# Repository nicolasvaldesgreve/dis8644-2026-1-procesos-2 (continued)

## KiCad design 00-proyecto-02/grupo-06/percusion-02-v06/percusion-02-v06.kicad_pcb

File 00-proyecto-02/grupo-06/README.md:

# proyecto-02

## Grupo

Número de grupo: 06

Tema del grupo: **Percutores**. 

Integrantes:

- Catalina Catalán / [06-terroiblea](https://github.com/terroiblea/dis8644-2026-1-procesos-2/tree/main/06-terroiblea)
- Martina Echavarría / [10-martinaechavarria-stack](https://github.com/terroiblea/dis8644-2026-1-procesos-2/tree/main/10-martinaechavarria-stack)
- Nicolás Miranda / [18-Nicolas-Miranda1312](https://github.com/terroiblea/dis8644-2026-1-procesos-2/tree/main/18-Nicolas-Miranda1312)
- Vania paredes / [24-paredesvania](https://github.com/terroiblea/dis8644-2026-1-procesos-2/tree/main/24-paredesvania)
- Carla Pino / [25-coff4](https://github.com/terroiblea/dis8644-2026-1-procesos-2/tree/main/25-Coff4)

## Circuito 1

Lub-dub.  

### Descripción general/conceptual 1

Lub-dub hace exactamente lo que hace un corazón: **bombea**. Pero en vez de bombear sangre, bombea pulsos eléctricos. En vez de mantener vivo a un organismo, **mantiene vivo el ritmo**. Lub-dub late. A veces  *Tac. Tac. Tac*. Otras, *Dumb. Dumb. Dumb*. Con la misma indiferencia biológica con que tu corazón te despertó esta mañana, Lub-dub bombea energía guiada por un compás. Es un percutor. Es un metrónomo pero con actitud.

#### ¿Qué hace Lub-dub por ti?

- Permite ajustar el tempo y el carácter del golpe, desde un latido tranquilo de persona en reposo hasta los 180bpm de alguien que acaba de ver su nota de taller.
- Es clínicamente superior a un metrónomo porque suena cool y los metrónomos no.
- Científicos del Instituto Cardiovascular de Sonidos Raros han determinado que escuchar Lub-dub mientras estudias mejora la concentración en un 340%. Este dato no ha sido verificado.

### Descripción de funcionamiento 1

Lub-dub recibe 12V por un jack de alimentación, regulados internamente a 5V con un L7805. Su output es una señal de audio por un jack estéreo. Tiene cuatro potenciómetros que en conjunto controlan el tempo y el carácter del golpe.

El corazón del circuito es un oscilador construido con inversores Schmitt-trigger de los chips 40106 y 4069UBE. Un condensador se carga y descarga continuamente a través de resistencias variables: los potenciómetros cambian esas resistencias, lo que cambia qué tan rápido se carga el condensador y por lo tanto qué tan rápido late y cómo suena ese latido. La ventaja del Schmitt-trigger es que conmuta en voltajes distintos al subir y al bajar, lo que produce ese golpe brusco y limpio en vez de una transición suave. Antes de llegar al output, la señal pasa por una red de condensadores y resistencias que recorta el pulso y lo convierte en un impulso corto y acentuado. Ese recorte es lo que transforma la oscilación en un *tac* o un *dumb* dependiendo de cómo estén ajustados los potenciómetros.

### Falstad 1

Antes de armar cada circuito realizamos un testeo del flujo de la corriente de cada circuito. 

### Esquemático 1

Esquemático referencia 1: Logic Noise: Filters And Drums de Hackaday.

Esquemático intervenido:

### PCB 1

La imagen de referencia para desarrollar el diseño de la PCB fue sacada de internet (link en referencias bibliográficas)

### Documentación audiovisual 1

#### Video funcionamiento protoboard 1

#### Video proceso y cambios protoboard 1

## Circuito 2

Barry Benson.  

### Descripción general/conceptual 2

Barry Benson no es una abeja. **Es peor que una abeja**, es una abeja con complejos, quiere ser una mosca. Tiene la capacidad sobreinsectoide de reproducir exactamente ese sonido de mosca agonizante atrapada entre tu oreja y la almohada a las 3 de la madrugada. Es la representación en silicio de ese sonido, **Barry Benson pega zumbidos**. Un zumbido ondulante que sube y baja de intensidad como si el insecto se acercara y alejara de tu oído a voluntad propia. La ciencia no puede explicar del todo por qué suena exactamente así. Nosotros tampoco. Pero lo hace.

#### ¿Qué hace Barry Benson por ti?

- Reproduce con fidelidad perturbadora el sonido de un insecto atrapado entre tu oreja y la almohada.
- Permite ajustar el zumbido con cuatro potenciómetros para encontrar el tono exacto que más molesta a tu compañero de pieza.
- Según investigaciones del prestigioso Instituto de Zumbidología Aplicada de Concepción, la exposición prenatal al sonido de Barry Benson produce niños con oído absoluto y una relación complicada con los insectos.
- Suena como *bzzzZZZzzzbzzZZZZzbzz*. Como si alguien hubiera atrapado una abeja en un sintetizador analógico y ninguno de los dos estuviera contento con la situación.
  
### Descripción de funcionamiento 2

Barry Benson recibe 12V por un jack de alimentación, que el circuito reduce internamente a 5V usando un regulador L7805. Su único output es una señal de audio por un jack estéreo.

Cuando alguien usa Barry Benson, interactúa con cuatro potenciómetros. Cada uno controla la frecuencia de un oscilador independiente, en otras palabras, es básicamente qué tan rápido vibra cada "ala" de la abeja. El chip que hace posible todo esto es el 40106, que contiene seis inversores Schmitt-trigger, componentes que deciden cuándo una señal es alta o baja, produciendo oscilaciones estables. Las cuatro señales resultantes se mezclan a través de compuertas XOR del chip 4070. Una XOR produce señal solo cuando sus entradas son distintas, así que al combinar frecuencias similares pero no idénticas, la salida fluctúa a una velocidad igual a la diferencia entre ambas. Ese fenómeno es lo que hace que el volumen suba y baje de forma orgánica y le da a Barry ese carácter de insecto vivo que ningún preset de sintetizador ha logrado replicar con tanta dignidad.

### Falstad 2

### Esquemático 2

Esquemático referencia: Inharmonic square waves (página 238) de Make: Electronic Music from scratch.

Esquemático intervenido: 

### PCB 2

La imagen de referencia para desarrollar el diseño de la PCB fue sacada de internet (link en referencias bibliográficas)

### Documentación audiovisual 2

#### Video funcionamiento protoboard 2

#### Video proceso y cambios protoboard 2

## BOM

| Componente | Tipo | Cantidad | Precio (c/u) | Comprar |
|------------|------|----------|--------------|---------|
| Chip 4069UBE | Circuito Integrado | 1 | $1.100 | [Cabeza Cuadrada](https://www.cabezacuadrada.cl/product/cd4069/) |
| Chip CD40106BE | Circuito Integrado | 2 | $750 | [Cabeza Cuadrada](https://www.cabezacuadrada.cl/product/cd40106be/) |
| Potenciómetro 100K | Potenciómetro | 4 |  $490 | [Mechatronic Store](https://www.mechatronicstore.cl/potenciometro-rotacional-10k/) |
| Potenciómetro 250K | Potenciómetro | 4 | $495 | [Altronics](https://altronics.cl/potenciometro-lineal-250k-b250k) |
| Capacitor no polarizado 100nF | Condensador Cerámico | 6 |  $100 | [Mechatronic Store](https://www.mechatronicstore.cl/condensadores-ceramicos-distintos-valores/) |
| Capacitor no polarizado 10nF | Condensador Cerámico | 1 | $100 | [Mechatronic Store](https://www.mechatronicstore.cl/condensadores-ceramicos-distintos-valores/) |
| Capacitor polarizado 10uF 50V | Condensador Electrolítico | 6 |  $100 | [Mechatronic Store](https://www.mechatronicstore.cl/condensador-capacitorio-de-electrolitico-por-unidad-varios-valores/) |
| Capacitor polarizado 0.22uF 50V | Condensador Electrolítico | 1 |  $100 | [Mechatronic Store](https://www.mechatronicstore.cl/condensador-capacitorio-de-electrolitico-por-unidad-varios-valores/) |
| Capacitor polarizado 100uF 50V | Condensador Electrolítico | 4 | $100 | [Mechatronic Store](https://www.mechatronicstore.cl/condensador-capacitorio-de-electrolitico-por-unidad-varios-valores/) |
| Capacitor polarizado 1uF 50V | Condensador Electrolítico | 1 | $100 | [Mechatronic Store](https://www.mechatronicstore.cl/condensador-capacitorio-de-electrolitico-por-unidad-varios-valores/) |
| Resistencia 100K | Resistencia 1/2W | 1 |  $100 | [Mechatronic Store](https://www.mechatronicstore.cl/resistencias-electricas-1-2-w-1-unidad/) |
| Resistencia 1K | Resistencia 3W | 4 |  $200 | [Mechatronic Store](https://www.mechatronicstore.cl/resistencias-electricas-3w-por-unidad/) |
| Diodo 1N4007 | Diodo Rectificador | 2 | $200 | [Mechatronic Store](https://www.mechatronicstore.cl/diodo-rectificador-in4007-1n4007-4007/) |
| LED 3mm/5mm | LED | 3 |  $100 | [Mechatronic Store](https://www.mechatronicstore.cl/led-3mm-5mm/) |
| Regulador de voltaje L7805 | Regulador 5V DC | 2 | $490 | [Mechatronic Store](https://www.mechatronicstore.cl/regulador-limitador-de-voltaje-5v-dc/) |
| Chip CD4070BE | Circuito Integrado | 1 | - | [Mouser](https://www.mouser.cl/ProductDetail/Texas-Instruments/CD4070BE?qs=5WY7Uqh921w5Ya0dPgjorQ%3D%3D) |
| Protoboard 830 puntos | Protoboard MB102 | 2 | $3.790 | [Mechatronic Store](https://www.mechatronicstore.cl/breadboard-830-puntos-mb102/) |
| Barrel Jack Switch | Conector | 4 | — | Extraídos del LID |
| Switch 2 pines, 2 posiciones | Interruptor On/Off | 2 | $570 | [Katode](https://www.katode.cl/switches/1339-interruptor-switch-2-pines-on-off-corto.html) |

## Otros circuitos 

### Amplificador/salida 

Usamos la base anteriormente vista en el proyecto 01 con el Chip 386; circuito temporal de amplificador para sonar más alto y poder modificar el sonido final. Al modificarse ciertos parámetros (condensadores) cada placa sonaba distinto. Barry Benson funciona mejor con condensadores menores a 100 μF y Lub-dub funciona mejor con condensadores de 100 μF.    

## Colaboración con otros grupos

### ¿Cómo ayudamos a otros grupos?

#### Carla Pino:

- Ayudó a dos grupos a subir de forma correcta las carpetas del proyecto 2, específicamente el apartado de las versiones de esquemáticos y PCB. 
- Ayudó a distintos grupos a instalar bibliotecas externas de KiCad.

#### Martina Echavarría: 

- Ayudó a *Grupo 01* a cargar su batería.

#### Vania Paredes, Catalina Catalán y Nicolás Miranda: 

- Ayudaron a *Grupo 04* en indicar e instruir cómo conectar barrel y audio jack.

#### Nicolás Miranda: 

- Ayudó a *Grupo 05* a poner y buscar huellas en KiCad. 

### ¿Cómo nos ayudó otro grupo?

- El *Grupo 01* nos ayudó con las huellas (recordar comandos). 
- El *Grupo 01* nos prestó su batería para grabar porque la de nosotros se quedó sin carga.

Agradecimiento especial a Sebastián Sáez (Sae porque sabe) que si bien no es del curso siempre está en el lid para prestarnos su super ayuda.

## Bibliografía

### Referencias Bibliográficas

- Akther, S. (s.f). *Vectores corazón real*. Vecteezy. <https://es.vecteezy.com/arte-vectorial/67973094-anatomico-humano-corazon-ilustraciones-anatomia-medico>
- Pearson, K. (2024). *Make: Electronic Music from scratch*. Make Community, LLC.  
- Stock,M. (25 de Febrero, 2026). *Silueta simple en negro y blanco de una abeja*.  Shutterstock. <https://www.shutterstock.com/es/image-vector/simple-black-white-silhouette-bee-representing-2743356303>
- Williams, E. (25 de Marzo, 2015). *Logic Noise: Filters And Drums*. Hackaday. <https://hackaday.com/2015/03/25/logic-noise-filters-and-drums/>

### Bibliografía investigación

- Klein, M. [@MoritzKlein0](10 de Agosto, 2023). *Designing a simple analog kick drum from scratch* [video]. Youtube. https://youtu.be/yz37Yz315eU
- Klein, M. [@MoritzKlein0](19 de Abril, 2024). *Designing a TR-808 style snare drum from scratch* [video]. Youtube. <https://youtu.be/hULEn2_4Unw>
- Klein, M. [@MoritzKlein0](5 de Diciembre, 2023). *Diseñando un hi-hat estilo TR-606 desde cero* [video]. Youtube. <https://youtu.be/zbBY7JL9nnQ>
- Pekkarinen, L. [@krakenpine](6 de Diciembre, 2020). *Diy Twin-T kick drum eurorack module demo* [video]. Youtube. <https://youtu.be/iETSEz60OVA>
- Pekkarinen, L. (2024). *k
rakenpine-synthing*. GitHub. 
<https://github.com/Krakenpine/krakenpine-synthing/tree/main>
- Newton C. (s.f). *Generadores de Percusión (ART858S)*. INCB. <https://www.incb.com.mx/index.php/articulos/9-articulos-tecnicos-y-proyectos/9910-generadores-de-percusion-art858s>
- Newton C. (s.f). *Generador de Percusión Para Ritmos Musicales (ART1596S)*. INCB. <https://newtoncbraga.com.mx/articulos/9-articulos-tecnicos-y-proyectos/31055-generador-de-percusion-para-ritmos-musicales-art1596s>
- Richardson, R. (23 de Marzo, 2013) *Twin T drum osc with 555 trigger*. Cirfcuit-Lab. <https://www.circuitlab.com/circuit/eykayh/twin-t-drum-osc-with-555-trigger/>

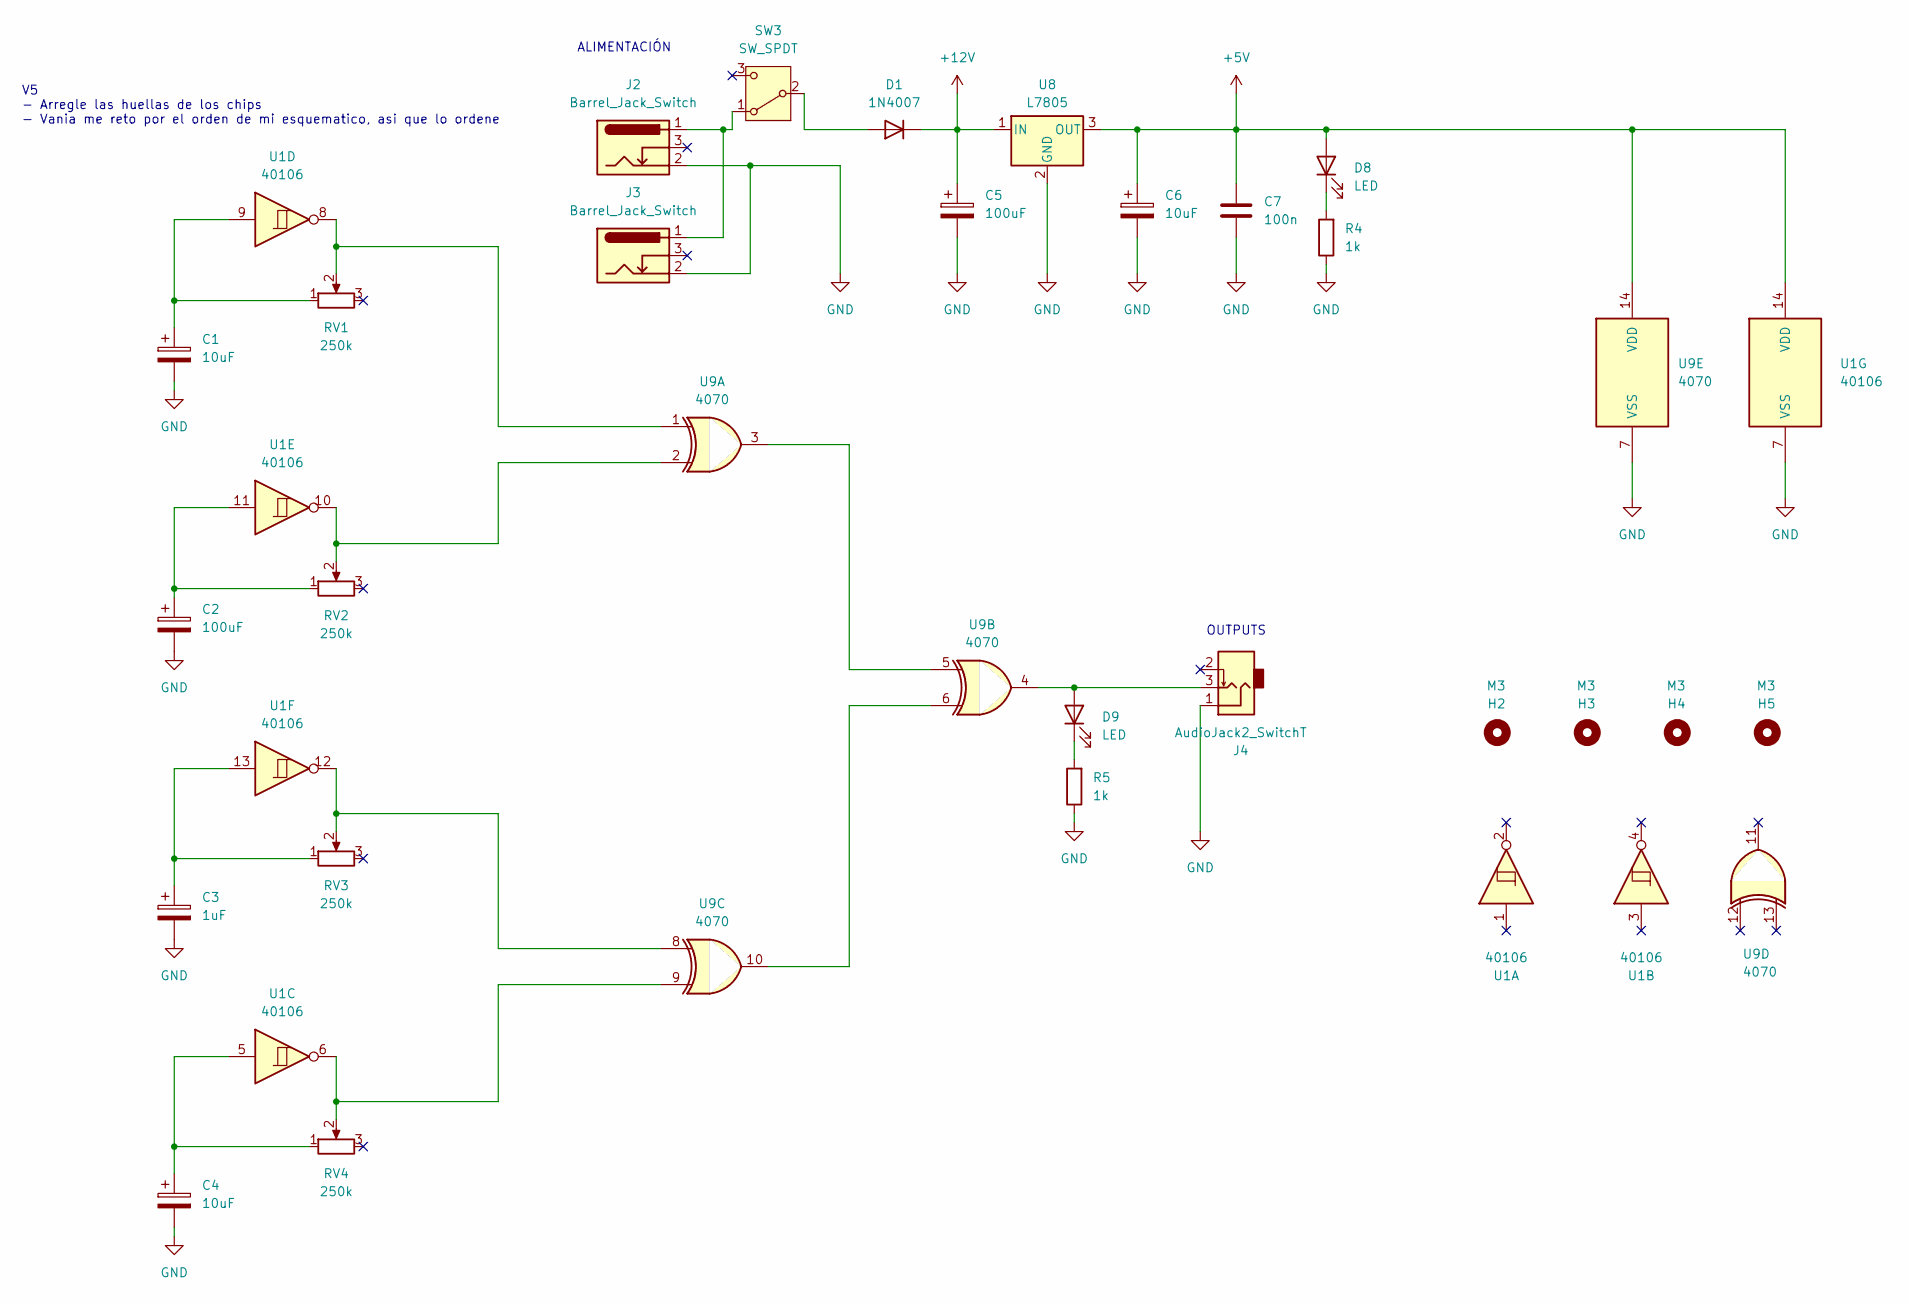
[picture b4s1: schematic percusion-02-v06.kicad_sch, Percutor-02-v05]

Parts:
C1, C4: 10uF; CP_Radial_D8.0mm_P3.80mm
C2, C5: 100uF; CP_Radial_D8.0mm_P3.80mm
C3: 1uF; CP_Radial_D8.0mm_P3.80mm
C6: 10uF; CP_Radial_D4.0mm_P2.00mm
C7: 100n; C_Disc_D5.0mm_W2.5mm_P2.50mm
D1: 1N4007; D_DO-41_SOD81_P10.16mm_Horizontal
D8, D9: LED; LED_D5.0mm
H2, H3, H4, H5: M3; MountingHole_3.2mm_M3
J2, J3: Barrel_Jack_Switch; BarrelJack_Horizontal
J4: AudioJack2_SwitchT; PJ301M-12
R4, R5: 1k; R_Axial_DIN0207_L6.3mm_D2.5mm_P10.16mm_Horizontal
RV1, RV2, RV3, RV4: 250k; Potentiometer_Alps_RK163_Single_Horizontal
SW3: SW_SPDT; spdt_ssd12d00g3
U1: 40106; DIP-14_W7.62mm_LongPads
U8: L7805; TO-220-3_Horizontal_TabDown
U9: 4070; DIP-14_W7.62mm_LongPads

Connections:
+5V: C6.1, C7.1, D8.2 (A), U1.14 (VDD), U8.3 (OUT), U9.14 (VDD)
+12V: C5.1, D1.1 (K), U8.1 (IN)
GND: C1.2, C2.2, C3.2, C4.2, C5.2, C6.2, C7.2, J2.2, J3.2, J4.1, R4.1, R5.1, U1.7 (VSS), U8.2 (GND), U9.7 (VSS)
unnamed: C1.1, RV1.1, U1.9
unnamed: C2.1, RV2.1, U1.11
unnamed: C3.1, RV3.1, U1.13
unnamed: C4.1, RV4.1, U1.5
unnamed: D1.2 (A), SW3.2 (B)
unnamed: D8.1 (K), R4.2
unnamed: D9.2 (A), J4.3, U9.4
unnamed: D9.1 (K), R5.2
unnamed: RV1.2, U1.8, U9.1
unnamed: RV2.2, U1.10, U9.2
unnamed: RV3.2, U1.12, U9.8
unnamed: RV4.2, U1.6, U9.9
unnamed: J2.1, J3.1, SW3.1 (A)
unnamed: U9.3, U9.5
unnamed: U9.6, U9.10

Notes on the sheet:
ALIMENTACIÓN
OUTPUTS
V5 - Arregle las huellas de los chips - Vania me reto por el orden de mi esquematico, asi que lo ordene

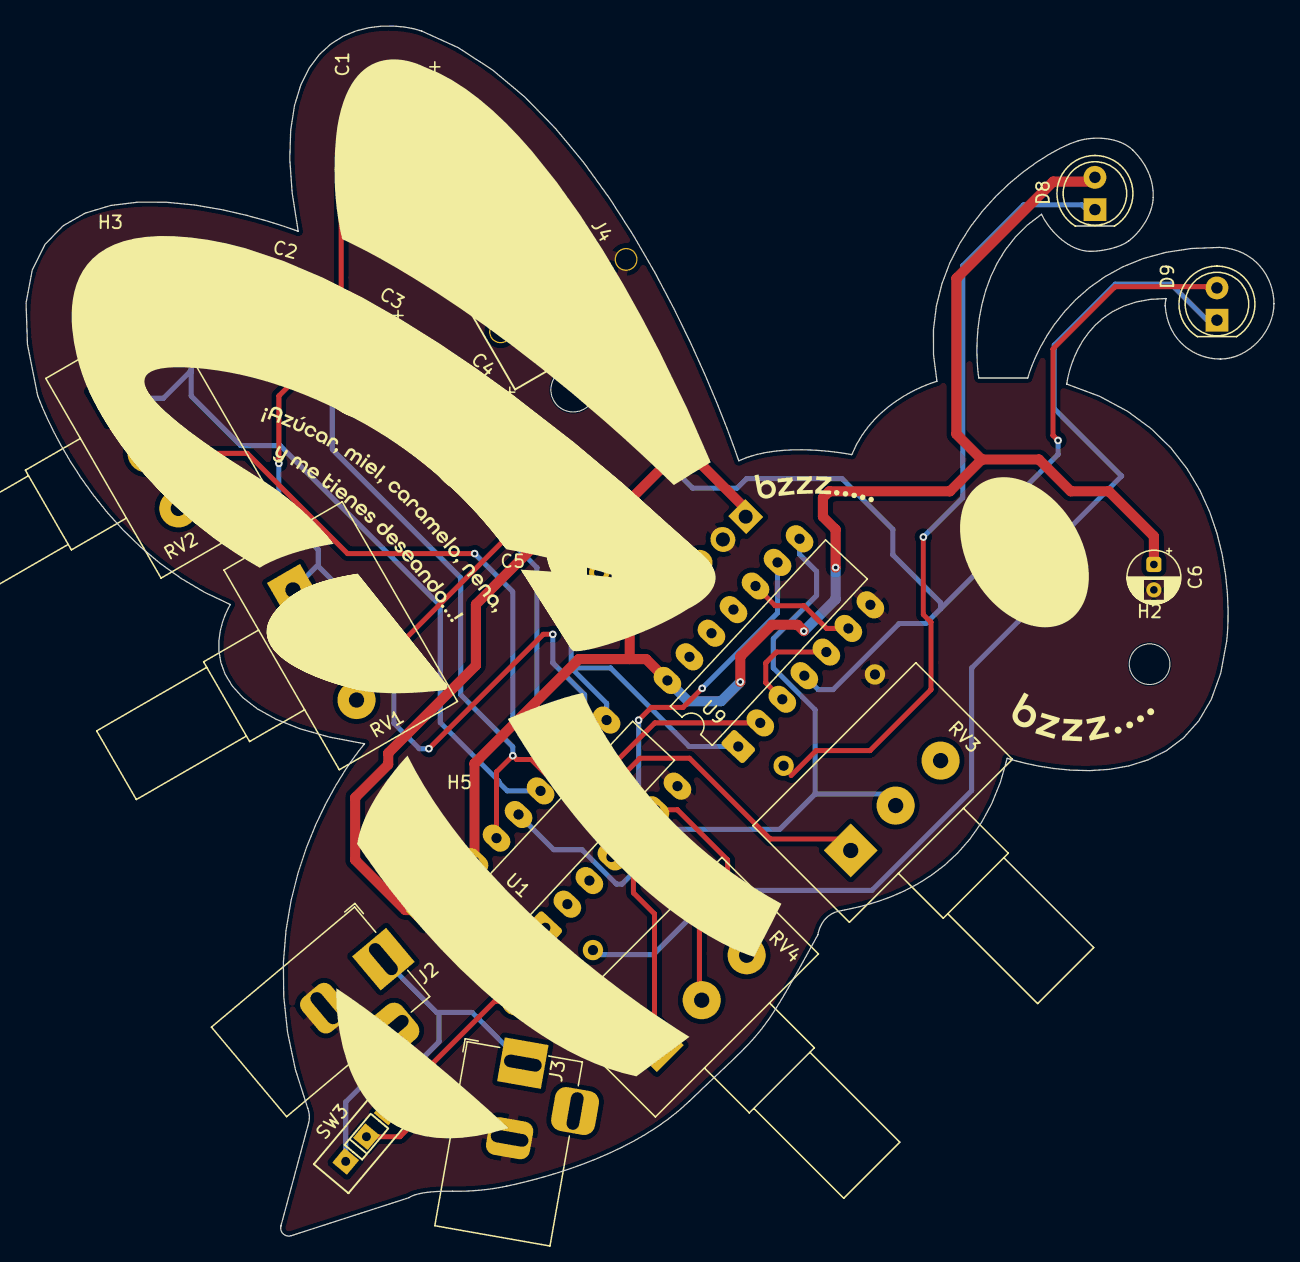
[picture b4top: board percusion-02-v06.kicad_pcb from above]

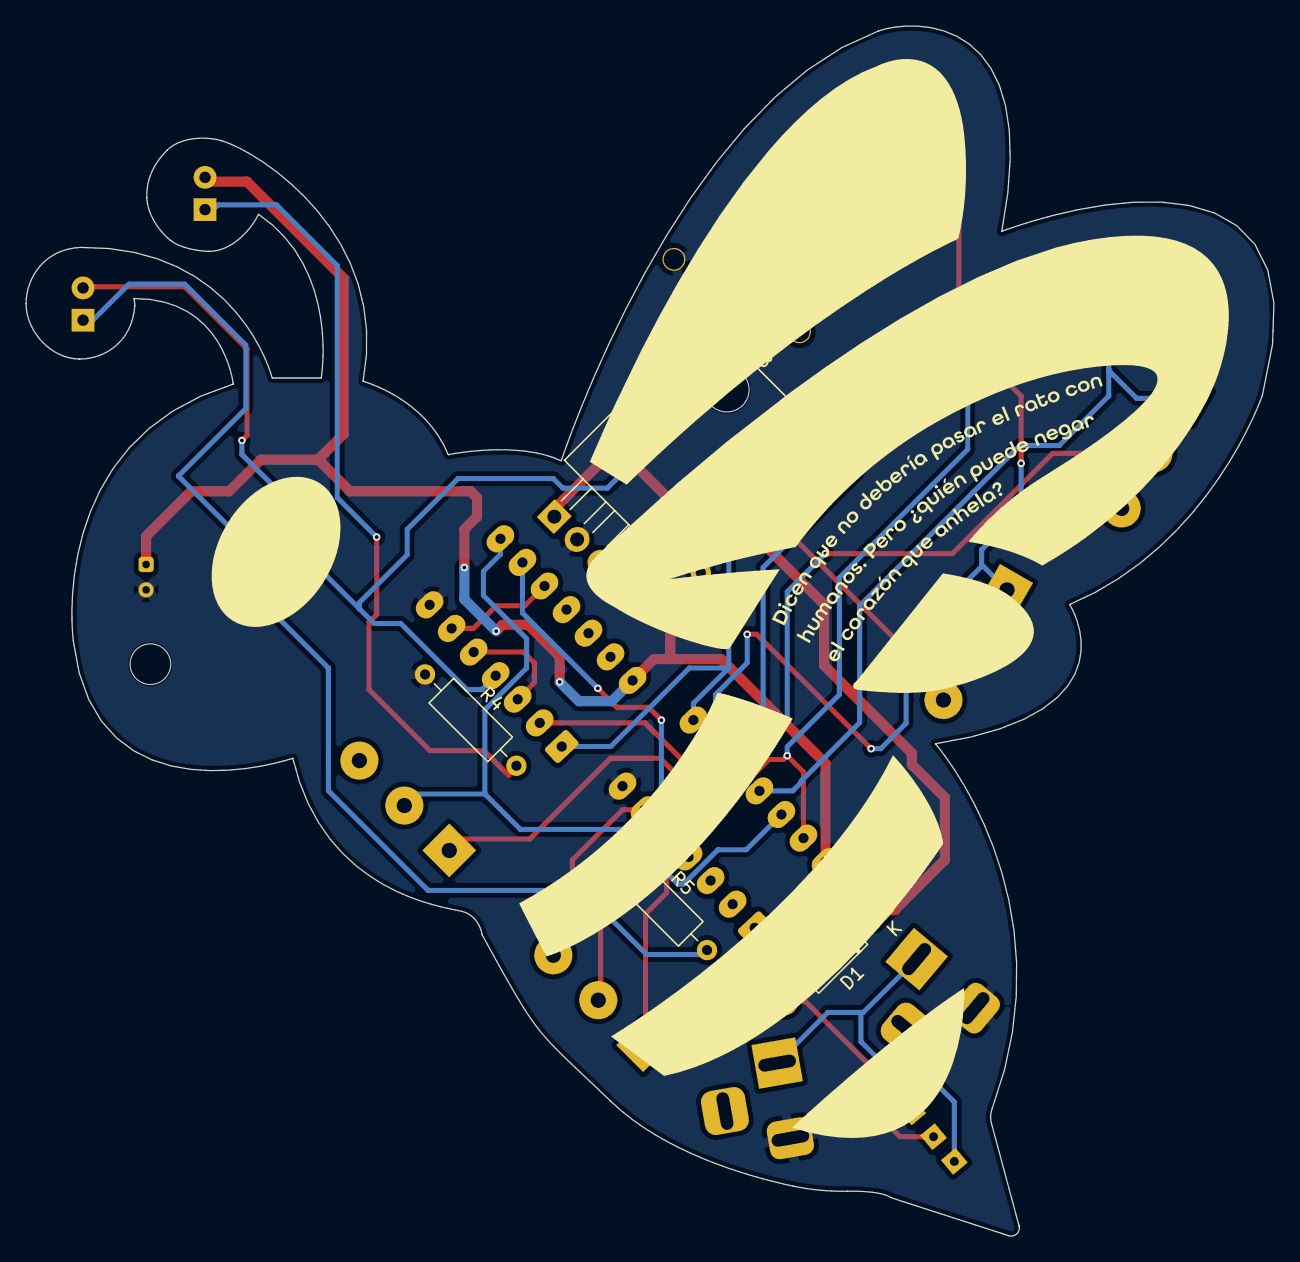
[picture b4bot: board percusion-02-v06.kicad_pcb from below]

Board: 2 copper layers, 98.2 x 95.2 mm, 26 parts (4 on the bottom side), 18 nets.

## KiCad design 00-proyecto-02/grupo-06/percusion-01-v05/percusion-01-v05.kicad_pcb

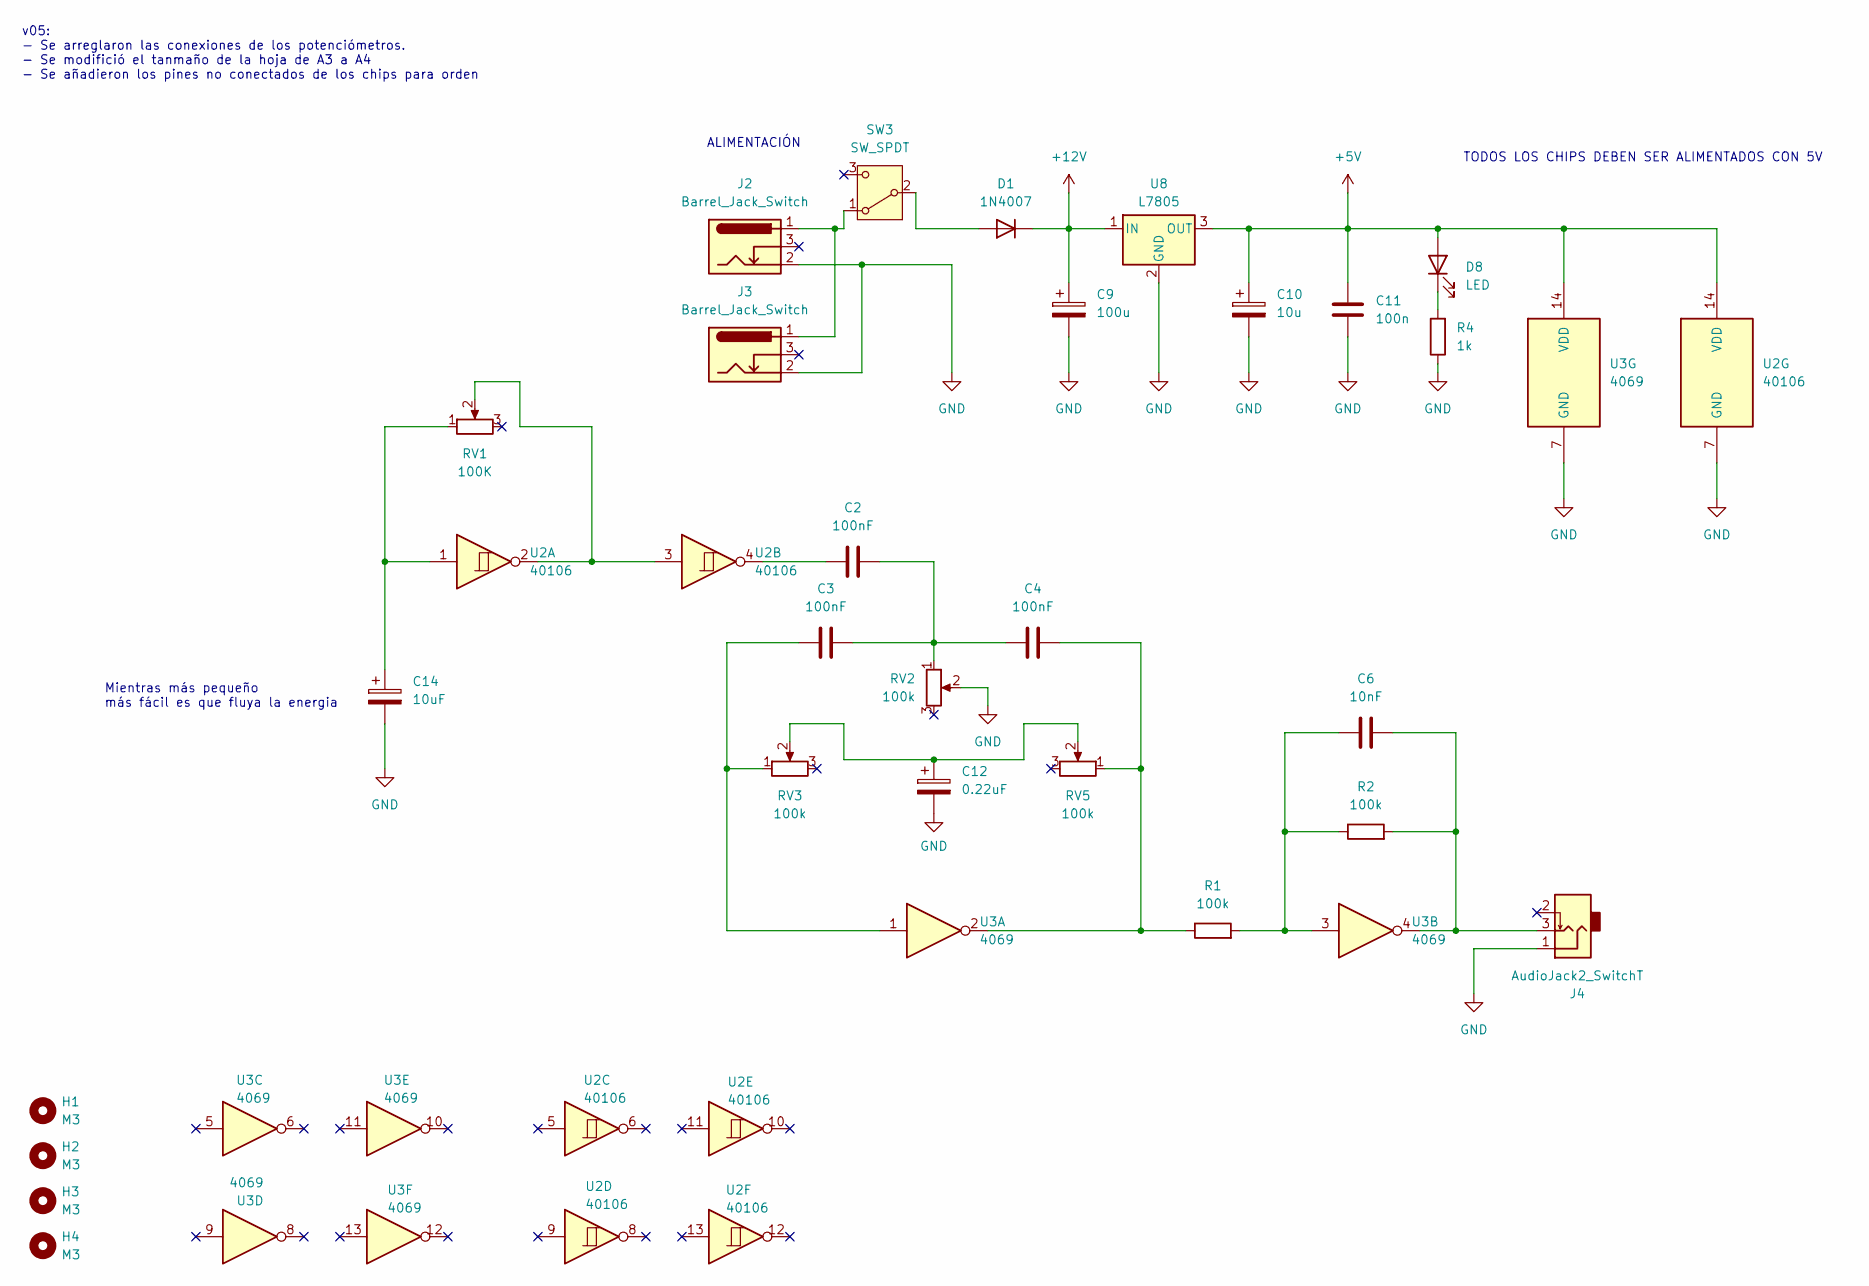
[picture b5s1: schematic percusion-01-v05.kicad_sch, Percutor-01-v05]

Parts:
C2, C3, C4: 100nF; C_Disc_D3.8mm_W2.6mm_P2.50mm
C6: 10nF; C_Disc_D3.8mm_W2.6mm_P2.50mm
C9: 100u; CP_Radial_D8.0mm_P3.80mm
C10: 10u; CP_Radial_D4.0mm_P2.00mm
C11: 100n; C_Disc_D5.0mm_W2.5mm_P2.50mm
C12: 0.22uF; CP_Radial_D8.0mm_P3.80mm
C14: 10uF; CP_Radial_D8.0mm_P3.80mm
D1: 1N4007; D_DO-41_SOD81_P10.16mm_Horizontal
D8: LED; LED_D5.0mm
H1, H2, H3, H4: M3; MountingHole_3.2mm_M3
J2, J3: Barrel_Jack_Switch; BarrelJack_Horizontal
J4: AudioJack2_SwitchT; PJ301M-12
R1, R2: 100k; R_Axial_DIN0207_L6.3mm_D2.5mm_P10.16mm_Horizontal
R4: 1k; R_Axial_DIN0207_L6.3mm_D2.5mm_P10.16mm_Horizontal
RV1: 100K; Potentiometer_Alps_RK163_Single_Horizontal
RV2, RV3, RV5: 100k; Potentiometer_Alps_RK163_Single_Horizontal
SW3: SW_SPDT; spdt_ssd12d00g3
U2: 40106; DIP-14_W7.62mm_LongPads
U3: 4069; DIP-14_W7.62mm_LongPads
U8: L7805; TO-220-3_Horizontal_TabDown

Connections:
+5V: C10.1, C11.1, D8.2 (A), U2.14 (VDD), U3.14 (VDD), U8.3 (OUT)
+12V: C9.1, D1.1 (K), U8.1 (IN)
GND: C9.2, C10.2, C11.2, C12.2, C14.2, J2.2, J3.2, J4.1, R4.1, RV2.2, U2.7 (GND), U3.7 (GND), U8.2 (GND)
unnamed: C2.1, U2.4
unnamed: C2.2, C3.2, C4.1, RV2.1
unnamed: C3.1, RV3.1, U3.1
unnamed: C4.2, R1.1, RV5.1, U3.2
unnamed: C6.1, R1.2, R2.1, U3.3
unnamed: C6.2, J4.3, R2.2, U3.4
unnamed: C12.1, RV3.2, RV5.2
unnamed: C14.1, RV1.1, U2.1
unnamed: D1.2 (A), SW3.2 (B)
unnamed: D8.1 (K), R4.2
unnamed: RV1.2, U2.2, U2.3
unnamed: J2.1, J3.1, SW3.1 (A)

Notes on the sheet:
TODOS LOS CHIPS DEBEN SER ALIMENTADOS CON 5V
ALIMENTACIÓN
v05: - Se arreglaron las conexiones de los potenciómetros. - Se modifició el tanmaño de la hoja de A3 a A4 - Se añadieron los pines no conectados de los chips para orden
Mientras más pequeño más fácil es que fluya la energia

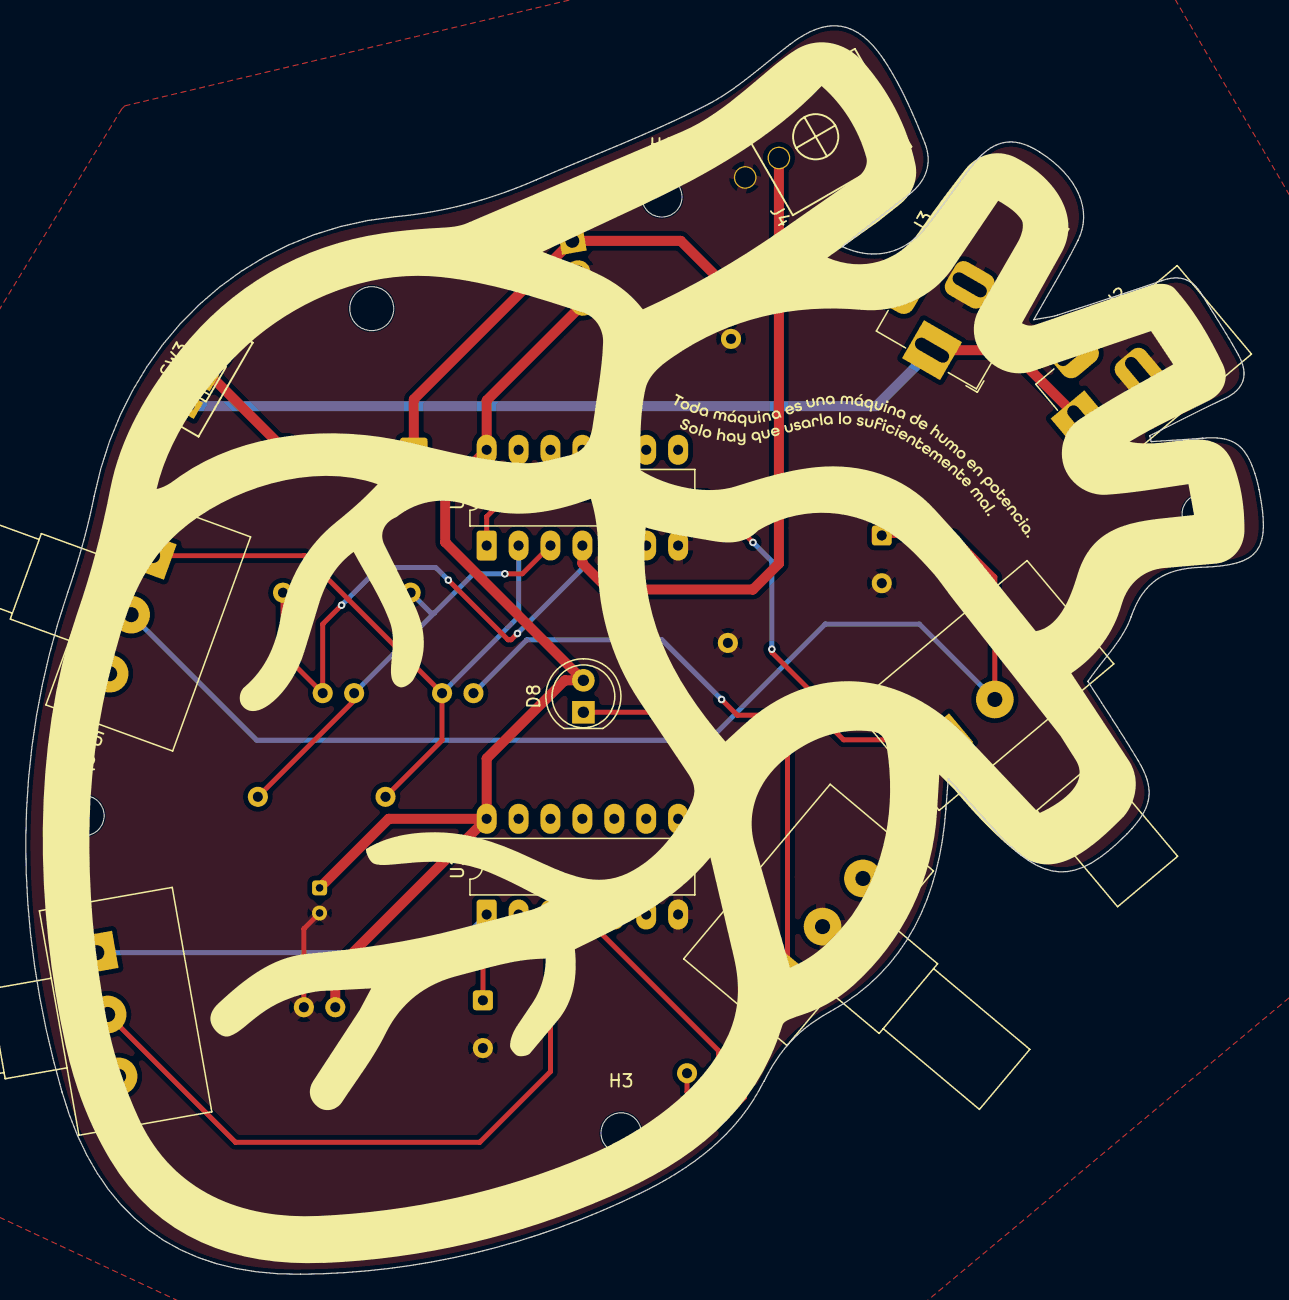
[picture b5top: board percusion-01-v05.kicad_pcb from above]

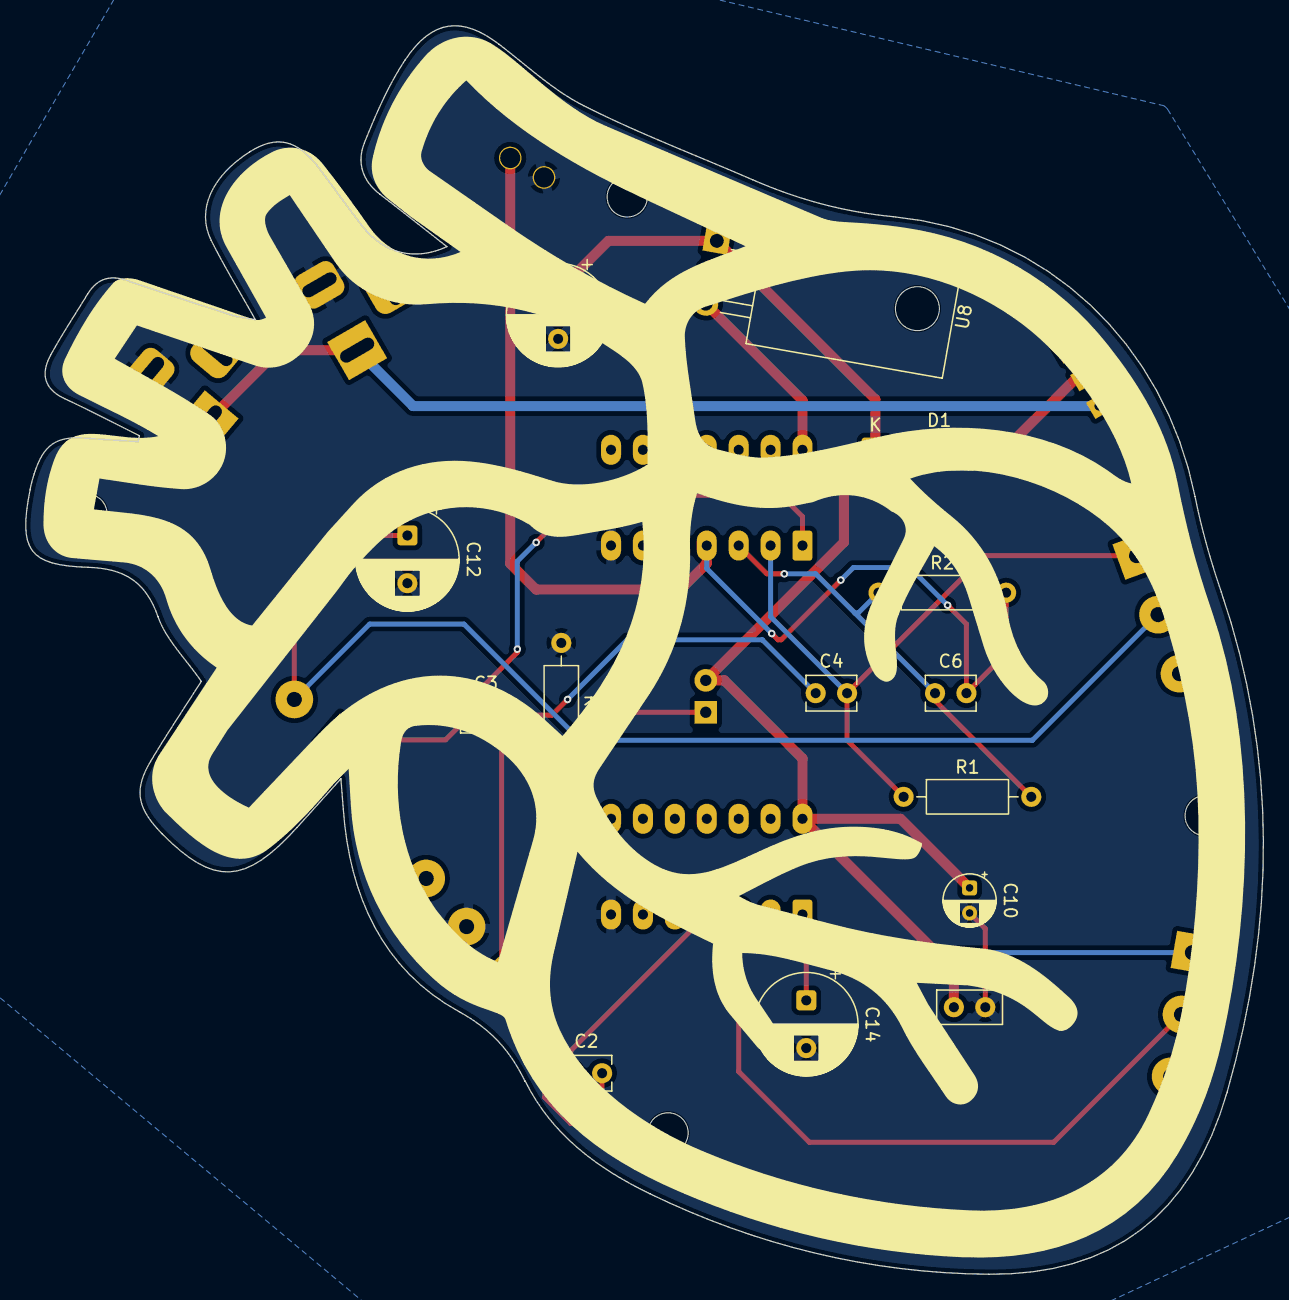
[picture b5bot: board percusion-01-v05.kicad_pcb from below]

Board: 2 copper layers, 98.5 x 99.4 mm, 29 parts (14 on the bottom side), 15 nets.

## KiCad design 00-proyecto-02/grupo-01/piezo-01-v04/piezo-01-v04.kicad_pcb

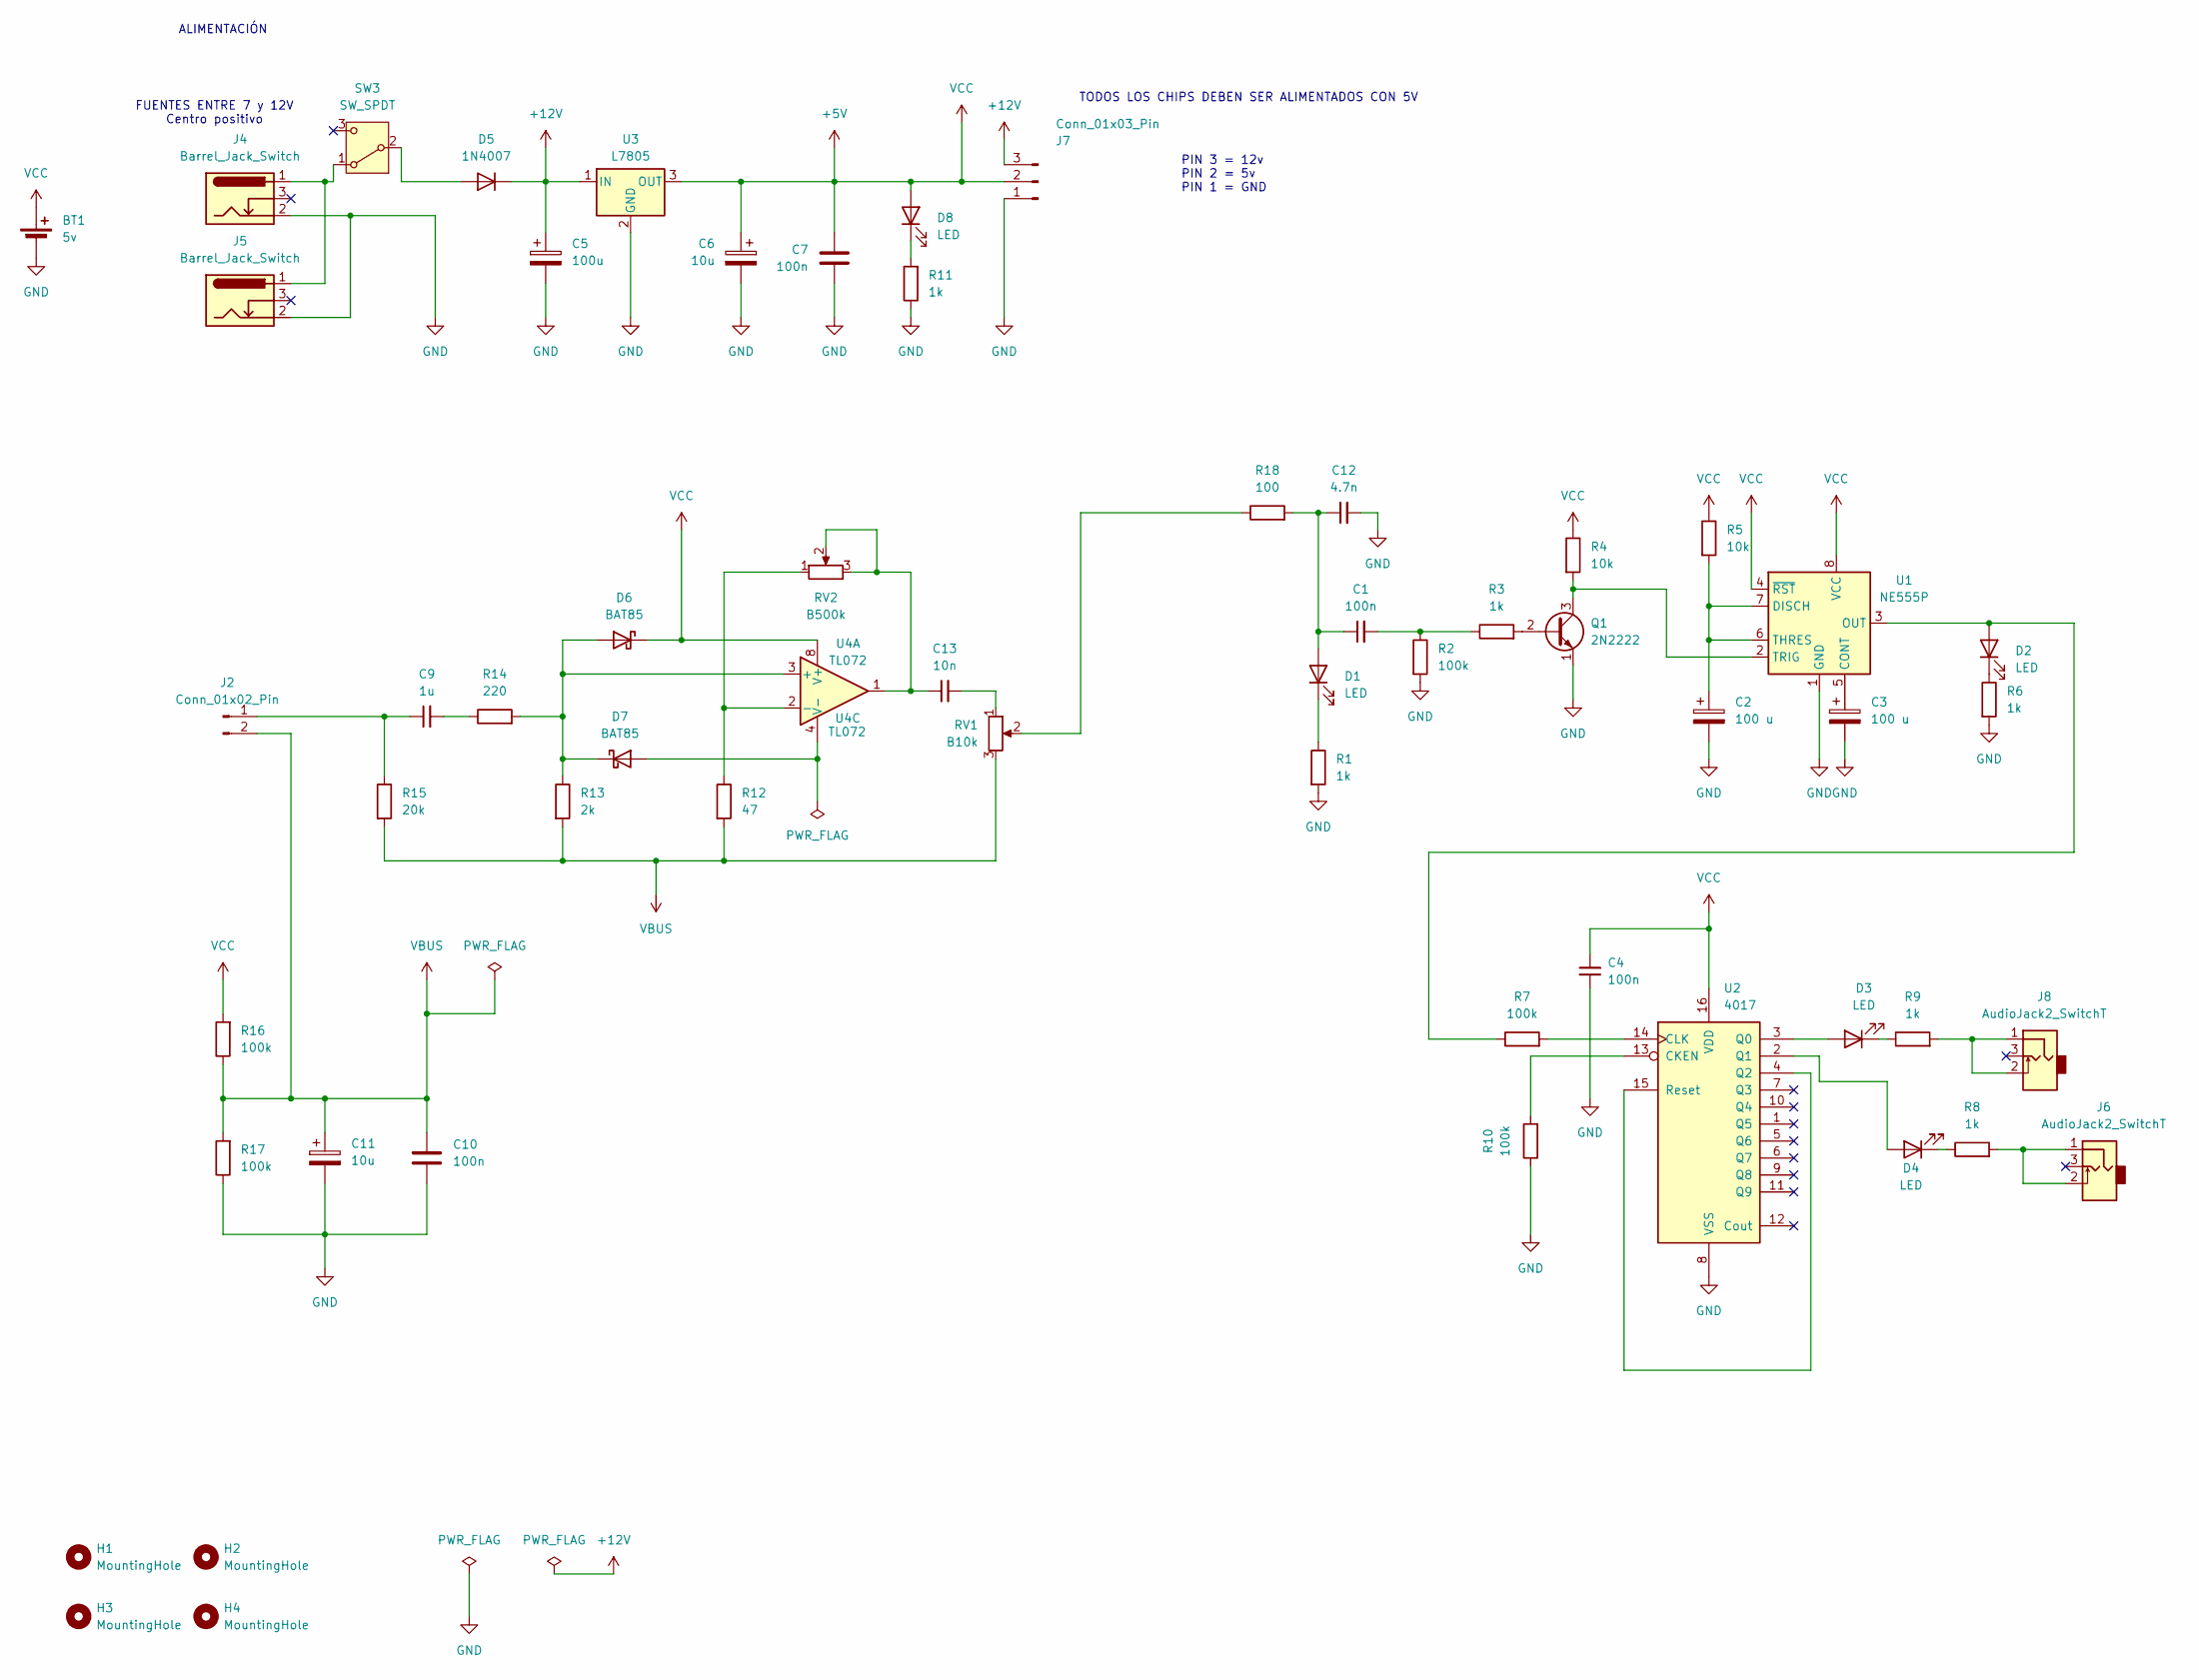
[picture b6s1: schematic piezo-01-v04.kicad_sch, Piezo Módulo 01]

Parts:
BT1: 5v; TerminalBlock_MaiXu_MX126-5.0-02P_1x02_P5.00mm
C1, C4, C7, C10: 100n; C_Disc_D5.0mm_W2.5mm_P2.50mm
C2, C3: 100 u; CP_Radial_D8.0mm_P3.80mm
C5: 100u; CP_Radial_D8.0mm_P3.80mm
C6, C11: 10u; CP_Radial_D4.0mm_P2.00mm
C9: 1u; C_Disc_D3.8mm_W2.6mm_P2.50mm
C12: 4.7n; C_Disc_D3.8mm_W2.6mm_P2.50mm
C13: 10n; C_Disc_D3.8mm_W2.6mm_P2.50mm
D1, D2, D3, D4, D8: LED; LED_D5.0mm
D5: 1N4007; D_DO-41_SOD81_P10.16mm_Horizontal
D6, D7: BAT85; D_DO-35_SOD27_P7.62mm_Horizontal
H1, H2, H3, H4: MountingHole; MountingHole_3.2mm_M3
J2: Conn_01x02_Pin; PinSocket_1x02_P2.54mm_Vertical
J4, J5: Barrel_Jack_Switch; BarrelJack_Horizontal
J6, J8: AudioJack2_SwitchT; PJ301M-12
J7: Conn_01x03_Pin; PinSocket_1x03_P2.54mm_Vertical
Q1: 2N2222; TO-39-3
R1, R3, R6, R8, R9, R11: 1k; R_Axial_DIN0207_L6.3mm_D2.5mm_P10.16mm_Horizontal
R2, R7, R10, R16, R17: 100k; R_Axial_DIN0207_L6.3mm_D2.5mm_P10.16mm_Horizontal
R4, R5: 10k; R_Axial_DIN0207_L6.3mm_D2.5mm_P10.16mm_Horizontal
R12: 47; R_Axial_DIN0207_L6.3mm_D2.5mm_P10.16mm_Horizontal
R13: 2k; R_Axial_DIN0207_L6.3mm_D2.5mm_P10.16mm_Horizontal
R14: 220; R_Axial_DIN0207_L6.3mm_D2.5mm_P10.16mm_Horizontal
R15: 20k; R_Axial_DIN0207_L6.3mm_D2.5mm_P10.16mm_Horizontal
R18: 100; R_Axial_DIN0207_L6.3mm_D2.5mm_P10.16mm_Horizontal
RV1: B10k; Potentiometer_Alps_RK163_Single_Horizontal
RV2: B500k; Potentiometer_Alps_RK163_Single_Horizontal
SW3: SW_SPDT; spdt_ssd12d00g3
U1: NE555P; CERDIP-8_W7.62mm_SideBrazed_LongPads
U2: 4017; CERDIP-16_W7.62mm_SideBrazed_LongPads
U3: L7805; TO-220-3_Vertical
U4: TL072; CERDIP-8_W7.62mm_SideBrazed_LongPads

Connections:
+5V: BT1.1 (+), C4.2, C6.1, C7.1, D6.1 (K), D8.2 (A), J7.2, R4.1, R5.1, R16.2, U1.4 (~RST), U1.8 (VCC), U2.16 (VDD), U3.3 (OUT), U4.8 (V+)
+12V: C5.1, D5.1 (K), J7.3, U3.1 (IN)
GND: BT1.2 (-), C2.2, C3.2, C4.1, C5.2, C6.2, C7.2, C10.2, C11.2, C12.2, J4.2, J5.2, J7.1, Q1.1 (E), R1.2, R2.2, R6.2, R10.1, R11.1, R17.1, U1.1 (GND), U2.8 (VSS), U3.2 (GND)
unnamed: C1.2, R2.1, R3.1
unnamed: C9.2, R14.1
unnamed: C13.1, RV2.2, RV2.3, U4.1
unnamed: C13.2, RV1.1
unnamed: C1.1, C12.1, D1.2 (A), R18.2
unnamed: D1.1 (K), R1.1
unnamed: D2.2 (A), R7.1, U1.3 (OUT)
unnamed: D2.1 (K), R6.1
unnamed: D3.2 (A), U2.3 (Q0)
unnamed: D3.1 (K), R9.1
unnamed: D4.2 (A), U2.2 (Q1)
unnamed: D4.1 (K), R8.1
unnamed: D5.2 (A), SW3.2 (B)
unnamed: D6.2 (A), D7.1 (K), R13.1, R14.2, U4.3 (+)
unnamed: D7.2 (A), U4.4 (V-)
unnamed: D8.1 (K), R11.2
unnamed: C9.1, J2.1, R15.1
unnamed: J6.1, J6.2, R8.2
unnamed: J8.1, J8.2, R9.2
unnamed: Q1.2 (B), R3.2
unnamed: Q1.3 (C), R4.2, U1.2 (TRIG)
unnamed: R18.1, RV1.2
unnamed: J4.1, J5.1, SW3.1 (A)
unnamed: C3.1, U1.5 (CONT)
unnamed: C2.1, R5.2, U1.6 (THRES), U1.7 (DISCH)
unnamed: R10.2, U2.13 (CKEN)
unnamed: R7.2, U2.14 (CLK)
unnamed: U2.4 (Q2), U2.15 (Reset)
unnamed: R12.1, RV2.1, U4.2 (-)
VBUS: C10.1, C11.1, J2.2, R12.2, R13.2, R15.2, R16.1, R17.2, RV1.3

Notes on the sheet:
PIN 3 = 12v PIN 2 = 5v PIN 1 = GND
ALIMENTACIÓN
TODOS LOS CHIPS DEBEN SER ALIMENTADOS CON 5V
FUENTES ENTRE 7 y 12V Centro positivo
